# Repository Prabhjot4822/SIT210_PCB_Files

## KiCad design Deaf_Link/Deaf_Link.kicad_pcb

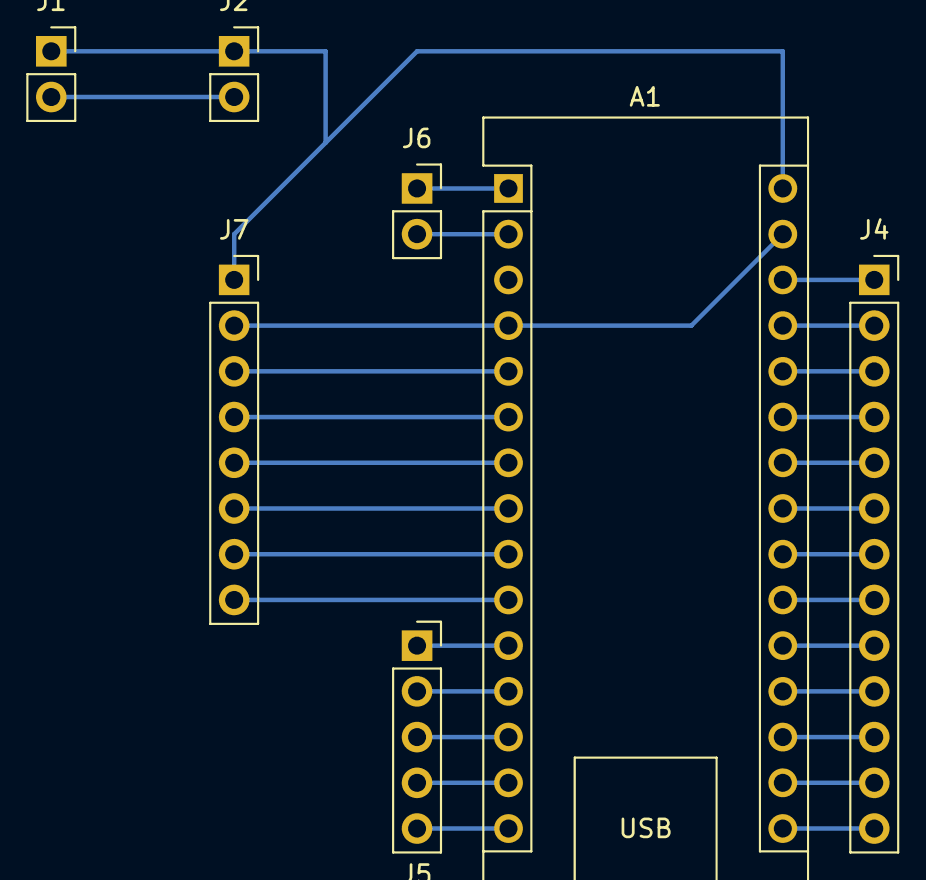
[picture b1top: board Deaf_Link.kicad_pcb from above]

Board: 2 copper layers, 7 parts (0 on the bottom side), 29 nets.

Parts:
A1: Arduino_Nano_v3.x; Arduino_Nano
J1: Main Power Input; PinSocket_1x02_P2.54mm_Vertical
J2: Motors Power Output; PinSocket_1x02_P2.54mm_Vertical
J4: Conn_01x13_Socket; PinSocket_1x13_P2.54mm_Vertical
J5: Conn_01x05_Socket; PinSocket_1x05_P2.54mm_Vertical
J6: Conn_01x02_Socket; PinSocket_1x02_P2.54mm_Vertical
J7: Nano Power Input and Motors Output; PinSocket_1x08_P2.54mm_Vertical

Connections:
+3.3V: A1.17 (3V3), J4.12
+5V: A1.27 (+5V), J4.2
/A1: A1.20 (A1), J4.9
/A2: A1.21 (A2), J4.8
/A3: A1.22 (A3), J4.7
/A4: A1.23 (A4), J4.6
/A5: A1.24 (A5), J4.5
/A6: A1.25 (A6), J4.4
/A7: A1.26 (A7), J4.3
/AO: A1.19 (A0), J4.10
/AREF: A1.18 (AREF), J4.11
/D2: A1.5 (D2), J7.3
/D3: A1.6 (D3), J7.4
/D4: A1.7 (D4), J7.5
/D5: A1.8 (D5), J7.6
/D6: A1.9 (D6), J7.7
/D7: A1.10 (D7), J7.8
/D8: A1.11 (D8), J5.1
/D9: A1.12 (D9), J5.2
/D10: A1.13 (D10), J5.3
/D11: A1.14 (D11), J5.4
/D12: A1.15 (D12), J5.5
/D13: A1.16 (D13), J4.13
/RST: A1.3 (~RESET), A1.28 (~RESET), J4.1
/RX0: A1.2 (D0/RX), J6.2
/TX1: A1.1 (D1/TX), J6.1
/VIN: A1.30 (VIN), J1.1, J2.1, J7.1
GND: A1.4 (GND), A1.29 (GND), J7.2
unnamed: J1.2, J2.2
